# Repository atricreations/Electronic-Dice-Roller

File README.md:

# Electronic-Dice-Roller.

Repository containing all the necessary files for the Electronic Dice Roller by Atricreations. 

There are 3 primary components to this repository:
- Code: The main micro python files for the RP2040 micro controller.
- 3D-Models: STL files that make up the case.
- PCB: Ki-cad PCB design files.

### What do this do?
This is the current iteration of a long running project seeking to implement electronic dice. This design features:
- RP2040 Microcontroller
- Fully RGB 5x7 matrix display
- Lithium battery and charger

The code is fully open source and the design is to encourage tinkering. The current design isn't perfect but is highly functional. As updates are made they will be posted here. 

 If you like what is here consider buying one or some of the components off of our Etsy. 
### How do I modify the software on my dice? 
 All complete dice come sold with the current version of software installed. If you would like to update the software you need to copy the files from the Code directory onto your device. Primarily this is done through [Thonny](https://thonny.org/). 
 
When a source file is opened on Thonny and the correct interface is selected, you can upload the new source file onto the micorcontroller. All files need to be updated for them to work properly. 

### I need help!!!!
Don't hesitate to email us at Atricreations@gmail.com if you need help with your unit. We may take a while to respond but we can offer help if needed. 

### History:
-V 0.1: 7/26/2024 -  Initial Beta Release - Highly functional, lacks low power features, a few small bugs. 

## Todo: 
### PCB:
- Add Accelerometer.
- Add Speaker.
### 3D Models:
- Improved Tolerances.
### Code:
- Improved low power performance (possibly port to circuitpython).
- Various bug fixes.
- Some type of config file to determine color encoding.
- Some type of encoding for animations and other effects.
- PC application to upload configurations.
- Endless feature creep. 

## License
Electronic Dice Roller © 2024 by Atricareations is licensed under CC BY-NC 4.0. To view a copy of this license, visit https://creativecommons.org/licenses/by-nc/4.0/

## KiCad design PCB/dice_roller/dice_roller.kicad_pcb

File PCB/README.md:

# PCB Design files
This folder contains the Ki-Cad design files for the pCB including the PCB and layout. 

There really isnt much to say here, if you are fammiliar with PCB design you'll know what to do. If not, feel free to ask questions but the design isnt completely trivial.

The design uses all LCSC parts and can be ordered fully assembled through JLCPCB.

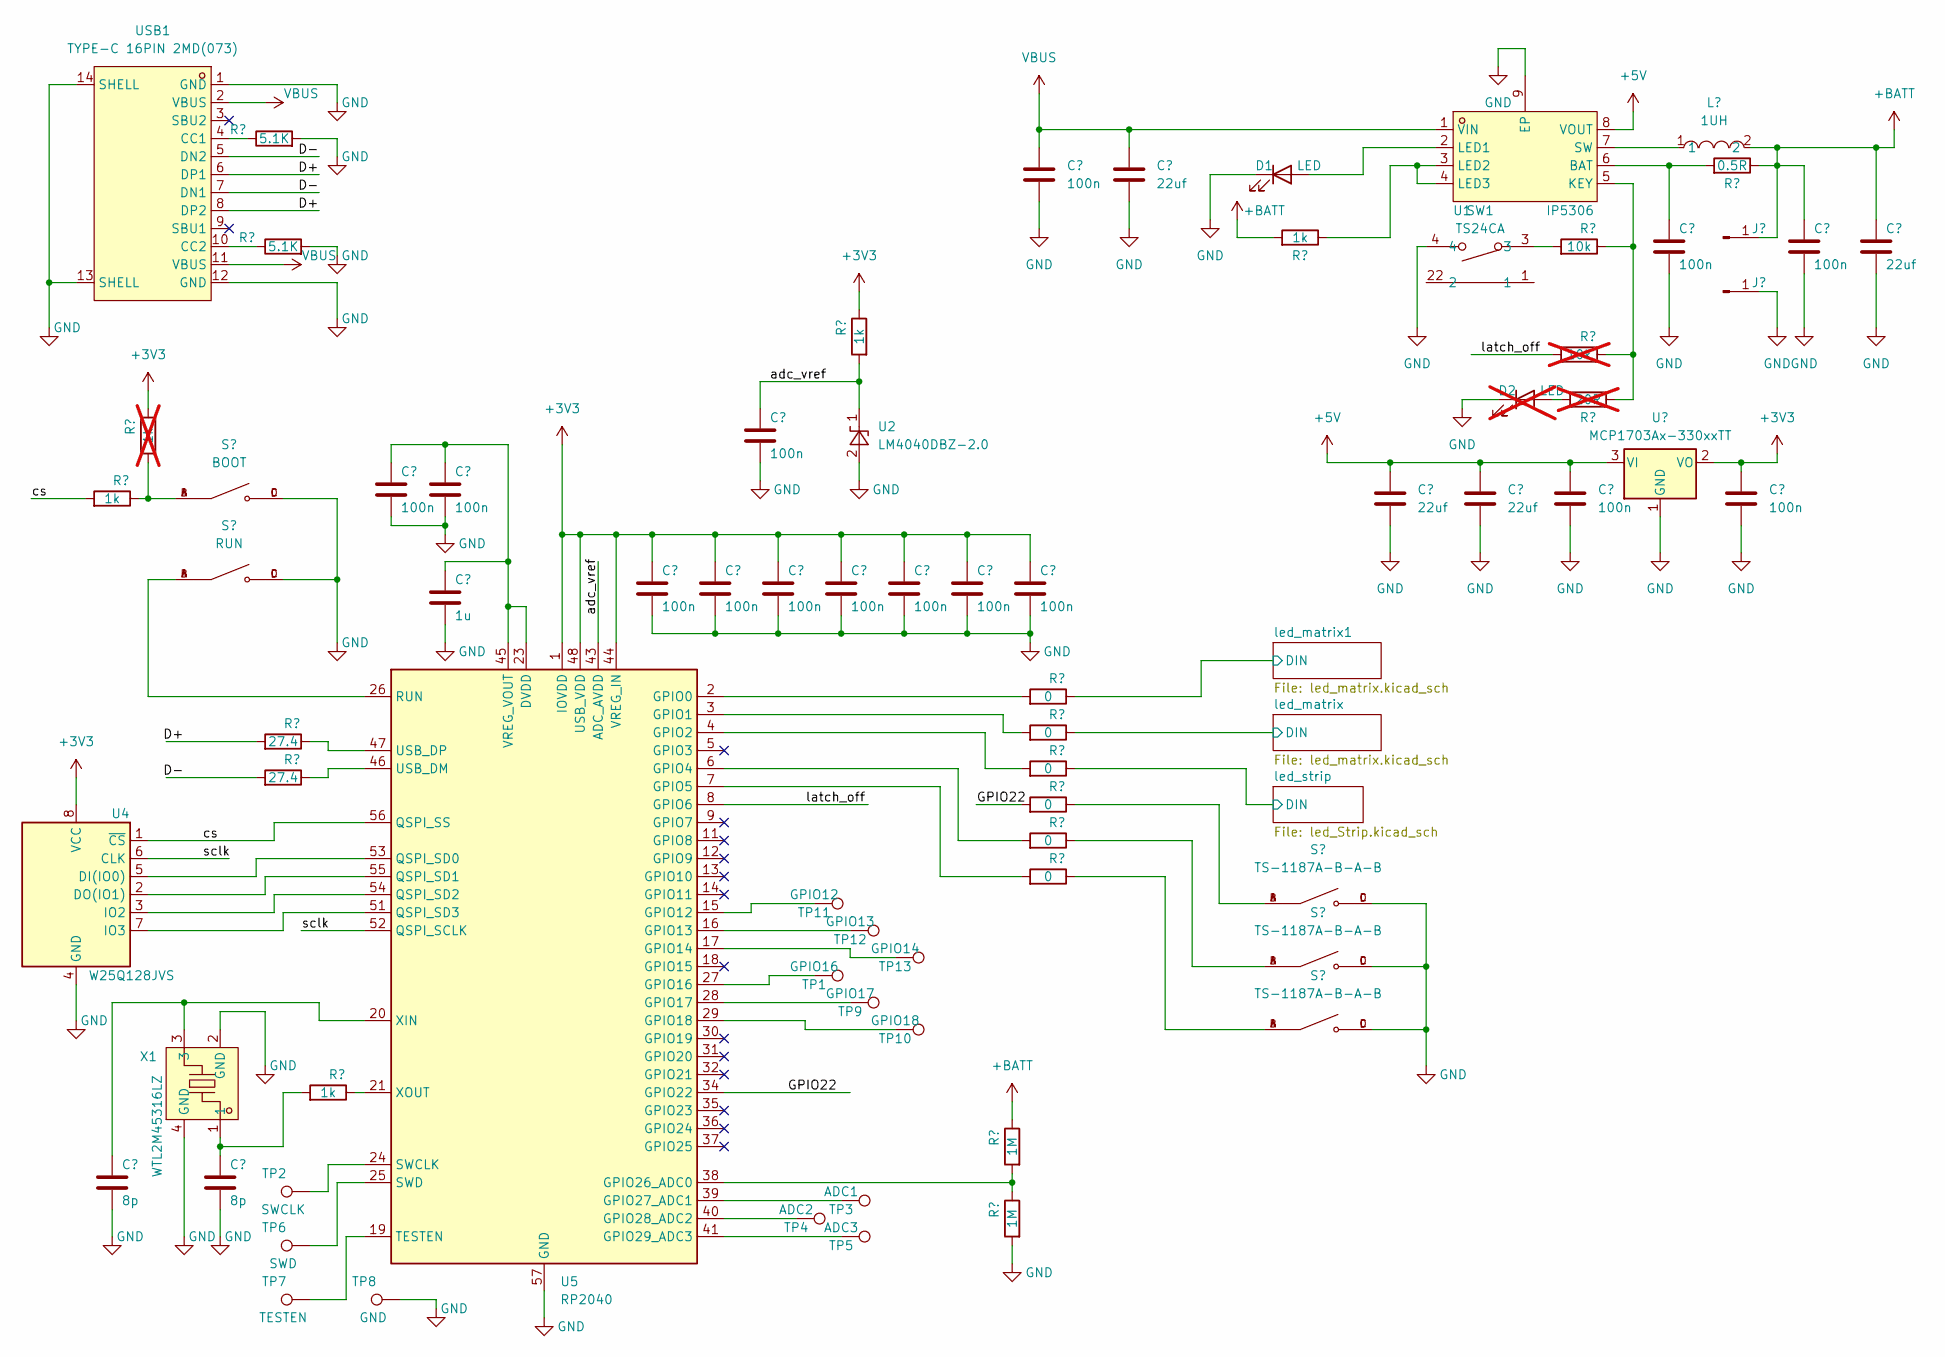
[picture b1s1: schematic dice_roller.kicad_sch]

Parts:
C1, C3, C4, C6, C7, C8, C11, C12, C13, C14, C15, C16, C17, C18, C19: 100n; C_0402_1005Metric
C2, C5, C9, C10: 22uf; C_0402_1005Metric
C20: 1u; C_0402_1005Metric
C21, C22: 8p; C_0402_1005Metric
D1: LED; LED_0603_1608Metric
D2: LED; LED_0603_1608Metric; not fitted
J1, J2: Conn_01x01_Pin; TestPoint_Pad_2.0x2.0mm
L1: 1UH; IND-SMD_L4.4-W4.2; LCSC Part C167203
R1, R3: 5.1K; R_0402_1005Metric
R2: 0.5R; R_0402_1005Metric
R4: 10k; R_0402_1005Metric
R5: 10k; R_0402_1005Metric; not fitted
R6, R8, R17, R20: 1k; R_0402_1005Metric
R7: 1k; R_0402_1005Metric; not fitted
R9, R10, R12, R14, R15, R16: 0; R_0402_1005Metric
R11, R13: 27.4; R_0402_1005Metric
R18, R19: 1M; R_0402_1005Metric
R21: 20R; R_0402_1005Metric; not fitted
S2: BOOT; SW_TS-1187A-B-A-B; PARTREV A0
S3: RUN; SW_TS-1187A-B-A-B; PARTREV A0
S4, S5, S6: TS-1187A-B-A-B; SW_TS-1187A-B-A-B; PARTREV A0
SW1: TS24CA; SW-SMD_TS24CA; LCSC Part C393942
TP1: GPIO16; TestPoint_Pad_D1.0mm
TP2: SWCLK; TestPoint_Pad_D1.0mm
TP3: ADC1; TestPoint_Pad_D1.0mm
TP4: ADC2; TestPoint_Pad_D1.0mm
TP5: ADC3; TestPoint_Pad_D1.0mm
TP6: SWD; TestPoint_Pad_D1.0mm
TP7: TESTEN; TestPoint_Pad_D1.0mm
TP8: GND; TestPoint_Pad_1.0x1.0mm
TP9: GPIO17; TestPoint_Pad_D1.0mm
TP10: GPIO18; TestPoint_Pad_D1.0mm
TP11: GPIO12; TestPoint_Pad_D1.0mm
TP12: GPIO13; TestPoint_Pad_D1.0mm
TP13: GPIO14; TestPoint_Pad_D1.0mm
U1: IP5306; ESOP-8_L4.9-W3.9-P1.27-LS6.0-BL-EP; LCSC Part C181692
U2: LM4040DBZ-2.0; SOT-23
U3: MCP1703Ax-330xxTT; SOT-23
U4: W25Q128JVS; SOIC-8_5.23x5.23mm_P1.27mm
U5: RP2040; QFN-56-1EP_7x7mm_P0.4mm_EP3.2x3.2mm
USB1: TYPE-C 16PIN 2MD(073); USB-C-SMD_TYPE-C-6PIN-2MD-073; LCSC Part C2765186
X1: WTL2M45316LZ; CRYSTAL-SMD_4P-L2.5-W2.0-BL; LCSC Part C963522

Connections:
+3V3: C12.1, C13.1, C14.1, C15.1, C16.1, C17.1, C18.1, C19.1, R6.1, R7.1, U3.2 (VO), U4.8 (VCC), U5.1 (IOVDD), U5.10 (IOVDD), U5.22 (IOVDD), U5.33 (IOVDD), U5.42 (IOVDD), U5.44 (VREG_IN), U5.48 (USB_VDD), U5.49 (IOVDD)
+5V: C9.1, C10.1, C11.1, U1.8 (VOUT), U3.3 (VI); also elsewhere on the board
+BATT: C4.1, C5.1, J1.1, L1.2, R2.1, R18.1, R20.2
/D+: R11.2, USB1.6 (DP1), USB1.8 (DP2)
/D-: R13.2, USB1.5 (DN2), USB1.7 (DN1)
/GPIO22: R14.2, U5.34 (GPIO22)
/adc_vref: C6.1, R6.2, U2.1 (K), U5.43 (ADC_AVDD)
/cs: R8.2, U4.1 (~CS), U5.56 (QSPI_SS)
/latch_off: R5.2, U5.8 (GPIO6)
/led_matrix1/DIN: R9.1; also elsewhere on the board
/led_matrix/DIN: R10.1; also elsewhere on the board
/led_strip/DIN: R12.1; also elsewhere on the board
/sclk: U4.6 (CLK), U5.52 (QSPI_SCLK)
GND: C1.2, C2.2, C3.2, C4.2, C5.2, C6.2, C7.2, C8.2, C9.2, C10.2, C11.2, C12.2, C13.2, C14.2, C15.2, C16.2, C17.2, C18.2, C19.2, C20.2, C21.2, C22.2, D1.1 (K), D2.1 (K), J2.1, R1.2, R3.2, R19.2, S2.C, S2.D, S3.C, S3.D, S4.C, S4.D, S5.C, S5.D, S6.C, S6.D, SW1.4, TP8.1, U1.9 (EP), U2.2 (A), U3.1 (GND), U4.4 (GND), U5.57 (GND), USB1.1 (GND), USB1.12 (GND), USB1.13 (SHELL), USB1.14 (SHELL), X1.2 (GND), X1.4 (GND); also elsewhere on the board
unnamed: C22.1, R17.2, X1.1
unnamed: D1.2 (A), U1.2 (LED1)
unnamed: D2.2 (A), R21.2
unnamed: R4.2, SW1.3
unnamed: R7.2, R8.1, S2.A, S2.B
unnamed: R14.1, S4.A, S4.B
unnamed: R15.1, S5.A, S5.B
unnamed: R16.1, S6.A, S6.B
unnamed: C3.1, R2.2, U1.6 (BAT)
unnamed: R4.1, R5.1, R21.1, U1.5 (KEY)
unnamed: R20.1, U1.3 (LED2), U1.4 (LED3)
unnamed: L1.1, U1.7 (SW)
unnamed: U4.5 (DI(IO0)), U5.53 (QSPI_SD0)
unnamed: U4.2 (DO(IO1)), U5.55 (QSPI_SD1)
unnamed: U4.3 (IO2), U5.54 (QSPI_SD2)
unnamed: U4.7 (IO3), U5.51 (QSPI_SD3)
unnamed: R9.2, U5.2 (GPIO0)
unnamed: R10.2, U5.3 (GPIO1)
unnamed: R12.2, U5.4 (GPIO2)
unnamed: R15.2, U5.6 (GPIO4)
unnamed: R16.2, U5.7 (GPIO5)
unnamed: TP11.1, U5.15 (GPIO12)
unnamed: TP12.1, U5.16 (GPIO13)
unnamed: TP13.1, U5.17 (GPIO14)
unnamed: TP1.1, U5.27 (GPIO16)
unnamed: TP9.1, U5.28 (GPIO17)
unnamed: TP10.1, U5.29 (GPIO18)
unnamed: R18.2, R19.1, U5.38 (GPIO26_ADC0)
unnamed: TP3.1, U5.39 (GPIO27_ADC1)
unnamed: TP4.1, U5.40 (GPIO28_ADC2)
unnamed: TP5.1, U5.41 (GPIO29_ADC3)
unnamed: S3.A, S3.B, U5.26 (RUN)
unnamed: TP2.1, U5.24 (SWCLK)
unnamed: TP6.1, U5.25 (SWD)
unnamed: TP7.1, U5.19 (TESTEN)
unnamed: R13.1, U5.46 (USB_DM)
unnamed: R11.1, U5.47 (USB_DP)
unnamed: C7.1, C8.1, C20.1, U5.23 (DVDD), U5.45 (VREG_VOUT), U5.50 (DVDD)
unnamed: C21.1, U5.20 (XIN), X1.3
unnamed: R17.1, U5.21 (XOUT)
unnamed: R1.1, USB1.4 (CC1)
unnamed: R3.1, USB1.10 (CC2)
VBUS: C1.1, C2.1, U1.1 (VIN), USB1.2 (VBUS), USB1.11 (VBUS)

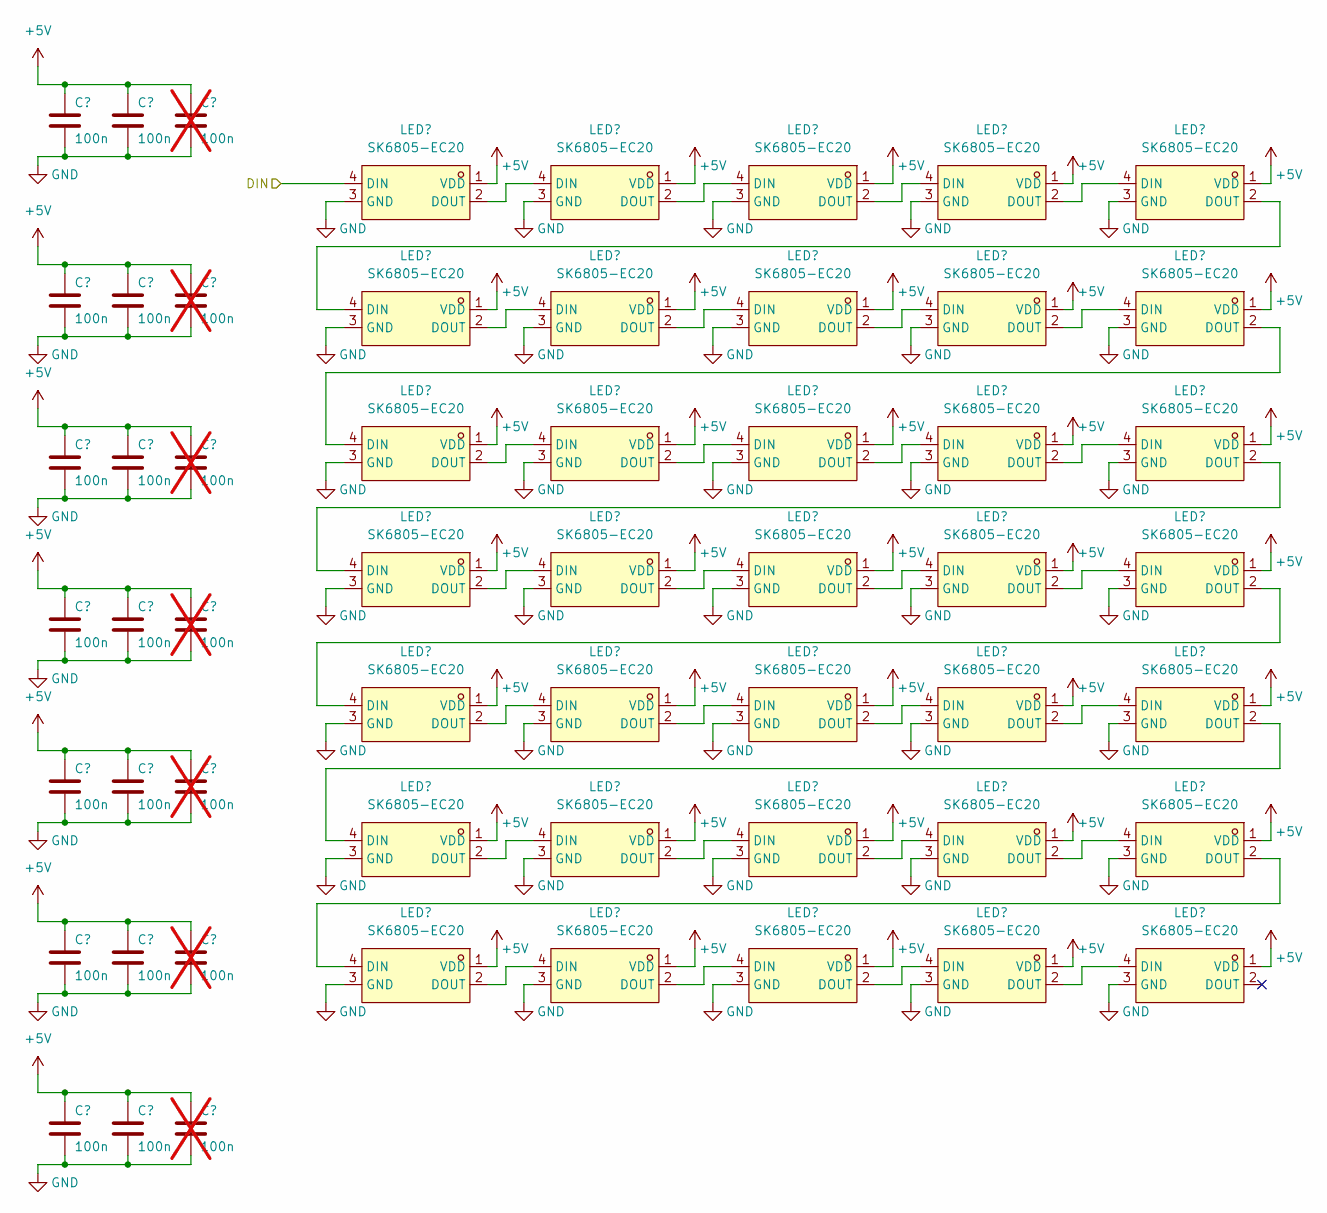
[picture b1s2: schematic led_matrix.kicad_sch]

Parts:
C23, C24, C26, C27, C29, C30, C32, C33, C35, C36, C38, C39, C41, C42: 100n; C_0402_1005Metric
C25, C28, C31, C34, C37, C40, C43: 100n; C_0402_1005Metric; not fitted
LED1, LED2, LED3, LED4, LED5, LED6, LED7, LED8, LED9, LED10, LED11, LED12, LED13, LED14, LED15, LED16, LED17, LED18, LED19, LED20, LED21, LED22, LED23, LED24, LED25, LED26, LED27, LED28, LED29, LED30, LED31, LED32, LED33, LED34, LED35: SK6805-EC20; LED-SMD_4P-L2.0-W2.0-BR; LCSC Part C2890036

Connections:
+5V: C23.1, C24.1, C25.1, C26.1, C27.1, C28.1, C29.1, C30.1, C31.1, C32.1, C33.1, C34.1, C35.1, C36.1, C37.1, C38.1, C39.1, C40.1, C41.1, C42.1, C43.1, LED1.1 (VDD), LED2.1 (VDD), LED3.1 (VDD), LED4.1 (VDD), LED5.1 (VDD), LED6.1 (VDD), LED7.1 (VDD), LED8.1 (VDD), LED9.1 (VDD), LED10.1 (VDD), LED11.1 (VDD), LED12.1 (VDD), LED13.1 (VDD), LED14.1 (VDD), LED15.1 (VDD), LED16.1 (VDD), LED17.1 (VDD), LED18.1 (VDD), LED19.1 (VDD), LED20.1 (VDD), LED21.1 (VDD), LED22.1 (VDD), LED23.1 (VDD), LED24.1 (VDD), LED25.1 (VDD), LED26.1 (VDD), LED27.1 (VDD), LED28.1 (VDD), LED29.1 (VDD), LED30.1 (VDD), LED31.1 (VDD), LED32.1 (VDD), LED33.1 (VDD), LED34.1 (VDD), LED35.1 (VDD); also elsewhere on the board
/led_matrix/DIN: LED1.4 (DIN); also elsewhere on the board
GND: C23.2, C24.2, C25.2, C26.2, C27.2, C28.2, C29.2, C30.2, C31.2, C32.2, C33.2, C34.2, C35.2, C36.2, C37.2, C38.2, C39.2, C40.2, C41.2, C42.2, C43.2, LED1.3 (GND), LED2.3 (GND), LED3.3 (GND), LED4.3 (GND), LED5.3 (GND), LED6.3 (GND), LED7.3 (GND), LED8.3 (GND), LED9.3 (GND), LED10.3 (GND), LED11.3 (GND), LED12.3 (GND), LED13.3 (GND), LED14.3 (GND), LED15.3 (GND), LED16.3 (GND), LED17.3 (GND), LED18.3 (GND), LED19.3 (GND), LED20.3 (GND), LED21.3 (GND), LED22.3 (GND), LED23.3 (GND), LED24.3 (GND), LED25.3 (GND), LED26.3 (GND), LED27.3 (GND), LED28.3 (GND), LED29.3 (GND), LED30.3 (GND), LED31.3 (GND), LED32.3 (GND), LED33.3 (GND), LED34.3 (GND), LED35.3 (GND); also elsewhere on the board
unnamed: LED1.2 (DOUT), LED2.4 (DIN)
unnamed: LED2.2 (DOUT), LED3.4 (DIN)
unnamed: LED3.2 (DOUT), LED4.4 (DIN)
unnamed: LED4.2 (DOUT), LED5.4 (DIN)
unnamed: LED5.2 (DOUT), LED6.4 (DIN)
unnamed: LED6.2 (DOUT), LED7.4 (DIN)
unnamed: LED7.2 (DOUT), LED8.4 (DIN)
unnamed: LED8.2 (DOUT), LED9.4 (DIN)
unnamed: LED9.2 (DOUT), LED10.4 (DIN)
unnamed: LED10.2 (DOUT), LED11.4 (DIN)
unnamed: LED11.2 (DOUT), LED12.4 (DIN)
unnamed: LED12.2 (DOUT), LED13.4 (DIN)
unnamed: LED13.2 (DOUT), LED14.4 (DIN)
unnamed: LED14.2 (DOUT), LED15.4 (DIN)
unnamed: LED15.2 (DOUT), LED16.4 (DIN)
unnamed: LED16.2 (DOUT), LED17.4 (DIN)
unnamed: LED17.2 (DOUT), LED18.4 (DIN)
unnamed: LED18.2 (DOUT), LED19.4 (DIN)
unnamed: LED19.2 (DOUT), LED20.4 (DIN)
unnamed: LED20.2 (DOUT), LED21.4 (DIN)
unnamed: LED21.2 (DOUT), LED22.4 (DIN)
unnamed: LED22.2 (DOUT), LED23.4 (DIN)
unnamed: LED23.2 (DOUT), LED24.4 (DIN)
unnamed: LED24.2 (DOUT), LED25.4 (DIN)
unnamed: LED25.2 (DOUT), LED26.4 (DIN)
unnamed: LED26.2 (DOUT), LED27.4 (DIN)
unnamed: LED27.2 (DOUT), LED28.4 (DIN)
unnamed: LED28.2 (DOUT), LED29.4 (DIN)
unnamed: LED29.2 (DOUT), LED30.4 (DIN)
unnamed: LED30.2 (DOUT), LED31.4 (DIN)
unnamed: LED31.2 (DOUT), LED32.4 (DIN)
unnamed: LED32.2 (DOUT), LED33.4 (DIN)
unnamed: LED33.2 (DOUT), LED34.4 (DIN)
unnamed: LED34.2 (DOUT), LED35.4 (DIN)

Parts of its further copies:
C44, C45, C47, C48, C50, C51, C53, C54, C56, C57, C59, C60, C62, C63: 100n; C_0402_1005Metric
C46, C49, C52, C55, C58, C61, C64: 100n; C_0402_1005Metric; not fitted
LED36, LED37, LED38, LED39, LED40, LED41, LED42, LED43, LED44, LED45, LED46, LED47, LED48, LED49, LED50, LED51, LED52, LED53, LED54, LED55, LED56, LED57, LED58, LED59, LED60, LED61, LED62, LED63, LED64, LED65, LED66, LED67, LED68, LED69, LED70: SK6805-EC20; LED-SMD_4P-L2.0-W2.0-BR; LCSC Part C2890036

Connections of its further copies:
+5V: C44.1, C45.1, C46.1, C47.1, C48.1, C49.1, C50.1, C51.1, C52.1, C53.1, C54.1, C55.1, C56.1, C57.1, C58.1, C59.1, C60.1, C61.1, C62.1, C63.1, C64.1, LED36.1 (VDD), LED37.1 (VDD), LED38.1 (VDD), LED39.1 (VDD), LED40.1 (VDD), LED41.1 (VDD), LED42.1 (VDD), LED43.1 (VDD), LED44.1 (VDD), LED45.1 (VDD), LED46.1 (VDD), LED47.1 (VDD), LED48.1 (VDD), LED49.1 (VDD), LED50.1 (VDD), LED51.1 (VDD), LED52.1 (VDD), LED53.1 (VDD), LED54.1 (VDD), LED55.1 (VDD), LED56.1 (VDD), LED57.1 (VDD), LED58.1 (VDD), LED59.1 (VDD), LED60.1 (VDD), LED61.1 (VDD), LED62.1 (VDD), LED63.1 (VDD), LED64.1 (VDD), LED65.1 (VDD), LED66.1 (VDD), LED67.1 (VDD), LED68.1 (VDD), LED69.1 (VDD), LED70.1 (VDD); also elsewhere on the board
/led_matrix1/DIN: LED36.4 (DIN); also elsewhere on the board
GND: C44.2, C45.2, C46.2, C47.2, C48.2, C49.2, C50.2, C51.2, C52.2, C53.2, C54.2, C55.2, C56.2, C57.2, C58.2, C59.2, C60.2, C61.2, C62.2, C63.2, C64.2, LED36.3 (GND), LED37.3 (GND), LED38.3 (GND), LED39.3 (GND), LED40.3 (GND), LED41.3 (GND), LED42.3 (GND), LED43.3 (GND), LED44.3 (GND), LED45.3 (GND), LED46.3 (GND), LED47.3 (GND), LED48.3 (GND), LED49.3 (GND), LED50.3 (GND), LED51.3 (GND), LED52.3 (GND), LED53.3 (GND), LED54.3 (GND), LED55.3 (GND), LED56.3 (GND), LED57.3 (GND), LED58.3 (GND), LED59.3 (GND), LED60.3 (GND), LED61.3 (GND), LED62.3 (GND), LED63.3 (GND), LED64.3 (GND), LED65.3 (GND), LED66.3 (GND), LED67.3 (GND), LED68.3 (GND), LED69.3 (GND), LED70.3 (GND); also elsewhere on the board
unnamed: LED36.2 (DOUT), LED37.4 (DIN)
unnamed: LED37.2 (DOUT), LED38.4 (DIN)
unnamed: LED38.2 (DOUT), LED39.4 (DIN)
unnamed: LED39.2 (DOUT), LED40.4 (DIN)
unnamed: LED40.2 (DOUT), LED41.4 (DIN)
unnamed: LED41.2 (DOUT), LED42.4 (DIN)
unnamed: LED42.2 (DOUT), LED43.4 (DIN)
unnamed: LED43.2 (DOUT), LED44.4 (DIN)
unnamed: LED44.2 (DOUT), LED45.4 (DIN)
unnamed: LED45.2 (DOUT), LED46.4 (DIN)
unnamed: LED46.2 (DOUT), LED47.4 (DIN)
unnamed: LED47.2 (DOUT), LED48.4 (DIN)
unnamed: LED48.2 (DOUT), LED49.4 (DIN)
unnamed: LED49.2 (DOUT), LED50.4 (DIN)
unnamed: LED50.2 (DOUT), LED51.4 (DIN)
unnamed: LED51.2 (DOUT), LED52.4 (DIN)
unnamed: LED52.2 (DOUT), LED53.4 (DIN)
unnamed: LED53.2 (DOUT), LED54.4 (DIN)
unnamed: LED54.2 (DOUT), LED55.4 (DIN)
unnamed: LED55.2 (DOUT), LED56.4 (DIN)
unnamed: LED56.2 (DOUT), LED57.4 (DIN)
unnamed: LED57.2 (DOUT), LED58.4 (DIN)
unnamed: LED58.2 (DOUT), LED59.4 (DIN)
unnamed: LED59.2 (DOUT), LED60.4 (DIN)
unnamed: LED60.2 (DOUT), LED61.4 (DIN)
unnamed: LED61.2 (DOUT), LED62.4 (DIN)
unnamed: LED62.2 (DOUT), LED63.4 (DIN)
unnamed: LED63.2 (DOUT), LED64.4 (DIN)
unnamed: LED64.2 (DOUT), LED65.4 (DIN)
unnamed: LED65.2 (DOUT), LED66.4 (DIN)
unnamed: LED66.2 (DOUT), LED67.4 (DIN)
unnamed: LED67.2 (DOUT), LED68.4 (DIN)
unnamed: LED68.2 (DOUT), LED69.4 (DIN)
unnamed: LED69.2 (DOUT), LED70.4 (DIN)

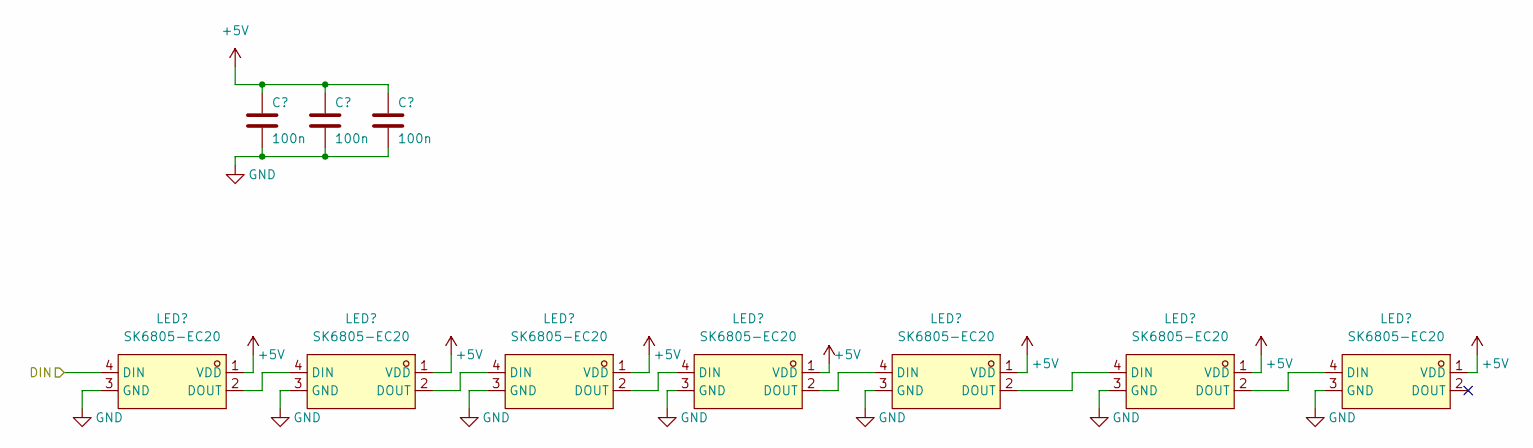
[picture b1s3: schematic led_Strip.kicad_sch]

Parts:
C65, C66, C67: 100n; C_0402_1005Metric
LED71, LED72, LED73, LED74, LED75, LED76, LED77: SK6805-EC20; LED-SMD_4P-L2.0-W2.0-BR; LCSC Part C2890036

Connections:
+5V: C65.1, C66.1, C67.1, LED71.1 (VDD), LED72.1 (VDD), LED73.1 (VDD), LED74.1 (VDD), LED75.1 (VDD), LED76.1 (VDD), LED77.1 (VDD); also elsewhere on the board
/led_strip/DIN: LED71.4 (DIN); also elsewhere on the board
GND: C65.2, C66.2, C67.2, LED71.3 (GND), LED72.3 (GND), LED73.3 (GND), LED74.3 (GND), LED75.3 (GND), LED76.3 (GND), LED77.3 (GND); also elsewhere on the board
unnamed: LED71.2 (DOUT), LED72.4 (DIN)
unnamed: LED72.2 (DOUT), LED73.4 (DIN)
unnamed: LED73.2 (DOUT), LED74.4 (DIN)
unnamed: LED74.2 (DOUT), LED75.4 (DIN)
unnamed: LED75.2 (DOUT), LED76.4 (DIN)
unnamed: LED76.2 (DOUT), LED77.4 (DIN)

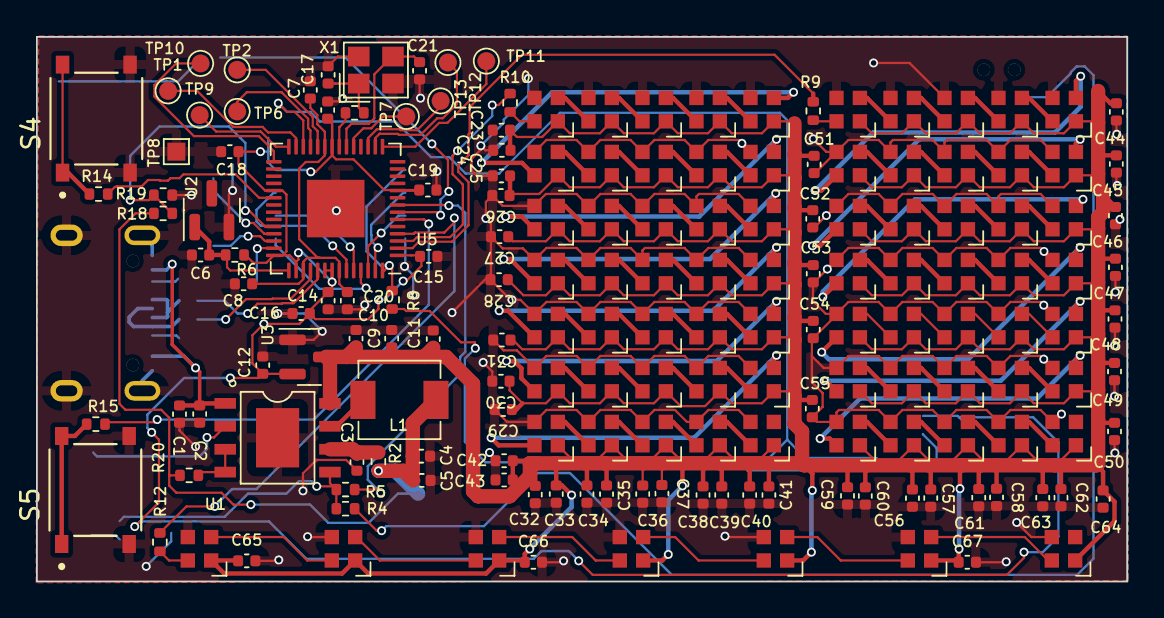
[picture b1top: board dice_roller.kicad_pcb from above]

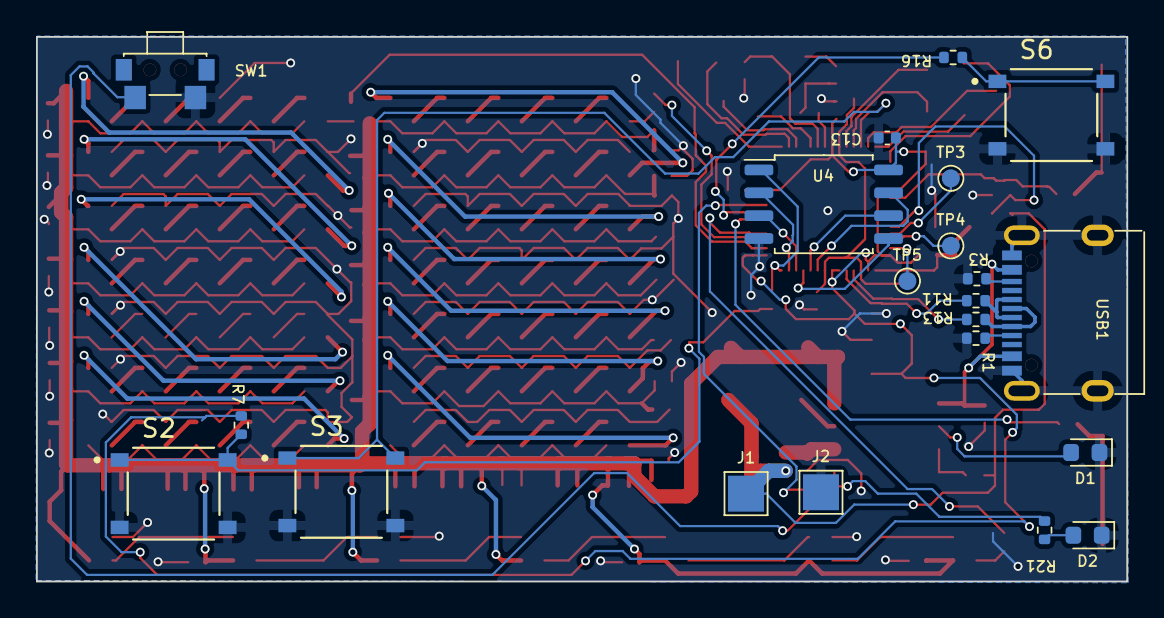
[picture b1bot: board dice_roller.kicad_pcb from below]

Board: 2 copper layers, 60.6 x 30.3 mm, 196 parts (21 on the bottom side), 131 nets.

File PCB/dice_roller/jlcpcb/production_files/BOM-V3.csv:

Comment,Designator,Footprint,LCSC
1k,"R17,R20,R6,R8",R_0402_1005Metric,C11702
22uf,"C10,C2,C5,C9",C_0402_1005Metric,C15525
8p,"C21,C22",C_0402_1005Metric,C161335
1UH,L1,IND-SMD_L4.4-W4.2,C167203
0,"R10,R12,R14,R15,R16,R9",R_0402_1005Metric,C17168
IP5306,U1,ESOP-8_L4.9-W3.9-P1.27-LS6.0-BL-EP,C181692
LED,D1,LED_0603_1608Metric,C2286
20R,R21,R_0402_1005Metric,C25092
10k,R4,R_0402_1005Metric,C25744
5.1K,"R1,R3",R_0402_1005Metric,C25905
1M,"R18,R19",R_0402_1005Metric,C26083
TYPE-C 16PIN 2MD(073),USB1,USB-C-SMD_TYPE-C-6PIN-2MD-073,C2765186
SK6805-EC20,"LED1,LED10,LED11,LED12,LED13,LED14,LED15,LED16,LED17,LED18,LED19,LED2,LED20,LED21,LED22,LED23,LED24,LED25,LED26,LED27,LED28,LED29,LED3,LED30,LED31,LED32,LED33,LED34,LED35,LED36,LED37,LED38,LED39,LED4,LED40,LED41,LED42,LED43,LED44,LED45,LED46,LED47,LED48,LED49,LED5,LED50,LED51,LED52,LED53,LED54,LED55,LED56,LED57,LED58,LED59,LED6,LED60,LED61,LED62,LED63,LED64,LED65,LED66,LED67,LED68,LED69,LED7,LED70,LED71,LED72,LED73,LED74,LED75,LED76,LED77,LED8,LED9",LED-SMD_4P-L2.0-W2.0-BR,C2890036
100n,"C1,C11,C12,C13,C14,C15,C16,C17,C18,C19,C23,C24,C25,C26,C27,C28,C29,C3,C30,C31,C32,C33,C34,C35,C36,C37,C38,C39,C4,C40,C41,C42,C43,C44,C45,C46,C47,C48,C49,C50,C51,C52,C53,C54,C55,C56,C57,C58,C59,C6,C60,C61,C62,C63,C64,C65,C66,C67,C7,C8",C_0402_1005Metric,C307331
27.4,"R11,R13",R_0402_1005Metric,C31439
BOOT,"S2,S3,S4,S5,S6",SW_TS-1187A-B-A-B,C318884
TS24CA,SW1,SW-SMD_TS24CA,C393942
LM4040DBZ-2.0,U2,SOT-23,C460725
0.5R,R2,R_0402_1005Metric,C5204041
1u,C20,C_0402_1005Metric,C52923
MCP1703Ax-330xxTT,U3,SOT-23,C5446
WTL2M45316LZ,X1,CRYSTAL-SMD_4P-L2.5-W2.0-BL,C963522
W25Q128JVS,U4,SOIC-8_5.23x5.23mm_P1.27mm,C97521
RP2040,U5,QFN-56-1EP_7x7mm_P0.4mm_EP3.2x3.2mm,

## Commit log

2024-07-27 added readmes
2024-07-27 added license
2024-07-27 oops
